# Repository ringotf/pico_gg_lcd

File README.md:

# Pico GG LCD

Work-in-progress update to Trirosmos' original RP2040 Game Gear mod.

More details on the [SMSPower Forum Thread](https://www.smspower.org/forums/20164-OpenSourceGameGearScreenReplacementPicoGGLCD)

## Project Status

Alpha. Main features have been proof-of-concepted, and a working prototype built based on the WL355608 branch (with minimal bodge-fixes). 
The firmware supports both Game Gear and Master System mode, but no adjustable scaling options yet.

> [!NOTE]
> **The PCB design is likely to see major changes.** The current build includes unneccessary placeholder components to be removed, amongst other things. The [WL355608-Dev](tree/WL355608_dev) branch will be updated with Beta changes first.

## "Working" Features

- 640x480 "HD" 3.5inch LCD WL-355608
- HDMI video output with stereo audio using [ikjordan PicoDVI branch](https://github.com/ikjordan/picodvi)
- LED Brightness control with Brightness Wheel
- On-Screen menu. For menu items. And other things.
- GG Mode at 4x horizontal, 3x vertical scaling
- SMS mode at 2x scaling
- [Installation Ribbon](#installation-ribbon)
- 3d printable screen holder

### Demo Video Link (Quiet/NoAudio):

### Another with better audio:

### PCB (Alpha Prototype 4)

## Issues/Upcoming Changes/ToDo

- The LCD connector ribbon is likely to be rotated 180 degrees, will make soldering easier for both LCD and HDMI connectors.
- The op-amps used for audio capture will probably be changed for a dual-op-amp instead of two singles.
- Audio has lots of interference, could be from the LCD mod, could be from the GG.
- The XC6206 3.3v regulator was used to try and eliminate noise from the Pico's onboard regulator interferring with ADC, but might be unneccessary now.
- Remove placeholder components in the audio circuit.
- Corrected LED backlight dimming circuit - currently uses 2 GPIO pins, plus a bodge as shown below.
- The GG Clock pin is no longer needed.
- HDMI Hot-Plug-Detect implemented with the spare Pico GPIO pin.
- Installation Ribbon needs updating to remove the GG Clock pin. 
- Memory. Firmware currently uses 2 framebuffers to help prevent tearing, but with all the other features the Pico is starting to stretch its 264KB RAM... rotating the LCD connector so the LCD is mounted up-right might help allow a single framebuffer and recover some memory for other features.
- The shift registers probably have more performance in them, might be able to work with 2 instead of 3 - might not be worth finding out?

### RP2040 vs RP2350B

Instead of using serial->parallel shift registers to implement the LCD RGB444 input, we could use the extra pins of the Pico2 48-GPIO RP2350B. These are more expensive even after excluding the cost of the 3x 74HC595 shift registers needed for the RP2040, but would simplify the PCB a lot... It was fun to make the project work on an RP2040!

Plus the extra ram of the RP2350 (520KB vs 264KB) will help allow other features to be added to the firmware.

## How It Works

The Game Gear outputs serial RGB444, which is captured using PIO programs and stored in a 16-Bit framebuffer. 
- GG video capture uses 7 GPIO pins: 4 data + 3 control. (*6 without GG Clock now, but anyway)
- PicoDVI output uses 8 GPIO pins.
- LED Backlight brightness control uses 2 GPIO pins.
- LCD requires 3 control signals, Reset, Clock and Data-Enable.

This is 20 pins for capture, HDMI output and LCD control, leaving **10** pins from the 30 GPIO Ultimate Pico.

The LCD expects parallel RGB for 640x480 60Hz. For RGB444 the lcd needs **12** input lines.

To feed the LCD with 12 data inputs, we can use serial-to-parallel shift registers to read data from the Pico serially over a few pins, and send to the LCD over 12 parallel pins.

Although the shift registers have their own timing limits, by using a combination of multiple registers and reusing the same data (scale the image horizontally by clocking the LCD up to 4 times) we can reduce the load on the individual register.

The outputs from the shift registers are interleaved to the LCD to avoid requiring any bit-shifting from the frame buffer.

So the Pico outputs 160 pixels of 12 bit data, with 4 bits per shift register clock to 3 shift registers, and then clocks the LCD 4x for an effective 640 pixels.
Using 5 GPIO pins: 3 MOSI, 1 shift register Latch, 1 shift register clock.

Which leaves a few GPIO pins for audio capture!

### Shift Register Diagram

Hopefully this diagram helps visually explain how the shift registers are wired in:

## Build Pics (Including backlight bodge)

### Assembled PCB Test

### Main Board Installed

### Main Board Testing

### Awaiting Closure

### Completed Build

## Installation Ribbon

There is an FPC Installation Ribbon project for easy soldering to the game gear main board. This is designed for the arms to be folded out to reach the various solder points.

## Schematic

Schematic PDF: [hw/GG_LCD_DIY.pdf](hw/GG_LCD_DIY.pdf)

## Gerbers/Bom

Main PCB Gerbers & Bom: [hw\jlcpcb\production_files](hw\jlcpcb\production_files)

Installation Ribbon Gerbers & Bom: [hw\InstallationRibbon\jlcpcb\production_files](hw\InstallationRibbon\jlcpcb\production_files)

Full details in the above files and KiCad project, but here's some of the highlights:

| Component | Description | Quantity |  Example Link(s) | 
| --- | --- | --- | --- |
| Pico GG LCD PCB | Printed Circuit Board | x1 |  |
| WL-355608 | 640x480 3.5" LCD<br />(Also sold as "RG35XX Replacement Screen") | x1 | https://www.aliexpress.com/item/1005005669918579.html <br /> https://www.aliexpress.com/item/1005007035513918.html |
| 30-GPIO Ultimate Pico | Purple RP2040 | x1 | https://www.aliexpress.com/item/1005005594351599.html <br /> https://www.aliexpress.com/item/1005007057526637.html |
| 54-Pin FPC Connector | LCD Ribbon Connector - Flip/Drawer "Bottom" | x1 | https://www.aliexpress.com/item/1005006818638048.html <br /> https://www.aliexpress.com/item/1005008569249941.html |
| 24-Pin FPC Connector | Data Connector - Flip/Drawer "Bottom" | x1 | https://www.aliexpress.com/item/1005006818638048.html <br /> https://www.aliexpress.com/item/1005008569249941.html |
| XC6206P332MR-G | 3.3v Regulator | x1 | https://www.aliexpress.com/item/33025330295.html |
| TPS61040DBVR | 20v Regulator | x1 | https://www.aliexpress.com/item/1005007852981529.html |
| [74HC595D](docs/sn74hc595.pdf) | Serial->Parallel Shift Registers | x3 | https://www.aliexpress.com/item/1005009410525894.html |
| [74HC165D](docs/sn74hc165.pdf) | Parallel->Serial Shift Register | x1 | https://www.aliexpress.com/item/1005009410525894.html |
| [SN74LVC4245APWR](docs/sn74lvc4245a.pdf) | Level-Shifting Transceiver | x1 | https://www.aliexpress.com/item/1005009206069625.html <br /> https://www.aliexpress.com/item/1005011552818805.html |
| [LMV321IDBVR](docs/lmv321.pdf) | Single Op-Amp | x2 | https://www.aliexpress.com/item/1005006127706764.html |
| HDMI Connector |  | x1 Optional | https://www.aliexpress.com/item/1005001412266648.html |
| DIY HDMI Connector | (See note below) | x2 Optional | https://www.aliexpress.com/item/1005004318851140.html <br /> https://www.aliexpress.com/item/1005006437300837.html |
| 20pin 0.5mm FFC | Flat cable for HDMI connectors<br />(Cheap but unshielded) | x1 Optional | https://www.aliexpress.com/item/1005007561337665.html |

Plus inductor, ferrite bead, diodes, capacitors, resistors, resistor network/arrays.

### DIY HDMI Cable Note

> [!WARNING]
> For DIY HDMI Cable, you need to buy **both Male and Female connector ends from the same listing** to ensure compatability with each other. 

Multiple listings included just as examples. If you mix-and-match across listings you might find the connector boards have different pinouts.

The cable requires a Type-A1 Male connector (the standard type) to connect to the PCB, plus a Female receptacle connector to be mounted inside the case, such as the Standard Type-A (often A4), or Micro-HDMI (often D4), or Mini-HDMI (Often C4) plus a 20cm FFC ribbon to join them together. (15cm is probably ok too)

The Micro-HDMI female connector is ideal for the minimising the size of the hole in the case, but still requires an appropriate Micro-HDMI cable or adapter to connect to a TV.

### DIY HDMI Examples 

### Micro-HDMI Shell Hole

### Micro-HDMI Connector Mounted

### Complete Micro-HDMI Install

### Don't Do This! Careful how the ribbon folds within the case!

# <br/><br/><br/>
### Original project readme for reference. This branch builds upon the fundamentals below:
<br/><br/>
# Pico GG LCD

RP2040-based Game Gear screen replacement kit.
Even a cheapo modern LCD has much, much, much better contrast ratio than the OG screen.

## Building the software

Clone this repository and pull all submodules:
```Bash
git clone https://github.com/Trirosmos/pico_gg_lcd
cd pico_gg_lcd
git submodule update --init --recursive
```

Then, run `sw/build.sh`:

```Bash
cd sw
mkdir build
cd build
cmake ../CMakeLists.txt
make
```

This should generate an uf2 file you can upload to the RP2040;

## Building the hardware

Componentes you'll need and their approximate cost:

- Pico GG LCD PCB ($5)
- [PMOD HDMI adapter board](https://aliexpress.com/w/wholesale-pmod%2525252dhdmi.html?spm=a2g0o.detail.search.0) ($4) 
- [54-pin FPC connector adapter board](https://aliexpress.com/item/32827105259.html) ($2)
- [LQ035NC111 LCD module](https://aliexpress.com/w/wholesale-LQ035NC111.html?spm=a2g0o.home.search.0) ($10)
- [RP2040 board that exposes all 30 GPIOs](https://aliexpress.com/item/1005003796653297.html) ($4)
- BS170 or similar NMOSFET ($0.3)
- ~470uH axial THT inductor ($0.2)
- 2x SOD-123 Schottky diode ($0.4)
- 10k 0805 resistor ($0.05)
- 100k 0805 resistor ($0.05)
- 100nF 0805 resistor ($0.05)
- 100uF 0805 resistor ($0.05)
- 22uF 0805 resistor ($0.05)

Total approximate BOM cost: $26

First assemble passive components and transistor, then the RP2040 board and leave the FPC connector to be connected last.
The final board should look something like this, sans the bodge wire:

## How Game Gear video signals work

The Game Gear ASIC generates digital video signals that the LCD drivers in the LCD ribbon use to drive the actual display segments.

In NTSC mode, i.e, when test pad T10 is connected to +5V, the timings of the signals from the ASIC closely resemble what one would expect from a console like the Master System. All screen replacement kits run the Game Gear in this mode, as far as I'm aware. 

The communication protocol used between the ASIC and the LCD drivers in this mode is [well documented](https://www.retrosix.wiki/va0va1-lcd-interface-game-gear) and essentially boils down to:

- 32 MHz pixel clock (same as the main system clock)
- 4 bit data bus carrying one channel of color data at a time
- VSync signal
- HSync signal

## How the RP2040 captures GG video

One of the PIOs is takes alongside three DMA channels with building a live framebuffer in RAM with the image data the GG is sending out.

Three PIO SMs are used in the following manner:

- SM0 detects when a frame starts and triggers an IRQ.
- SM1 detects the IRQ from SM0 and starts detecting HSync pulses. It triggers an IRQ when it does.
- SM2 detects the IRQ from SM1 and proceeds to capture pixel data and push it out to the RX FIFO.

One of the DMA channels then takes the 12bpp pixel data from the PIO RX FIFO and saves it into RAM.

Finally, one of the CPU cores upscales the image and sends it out to the LCD.

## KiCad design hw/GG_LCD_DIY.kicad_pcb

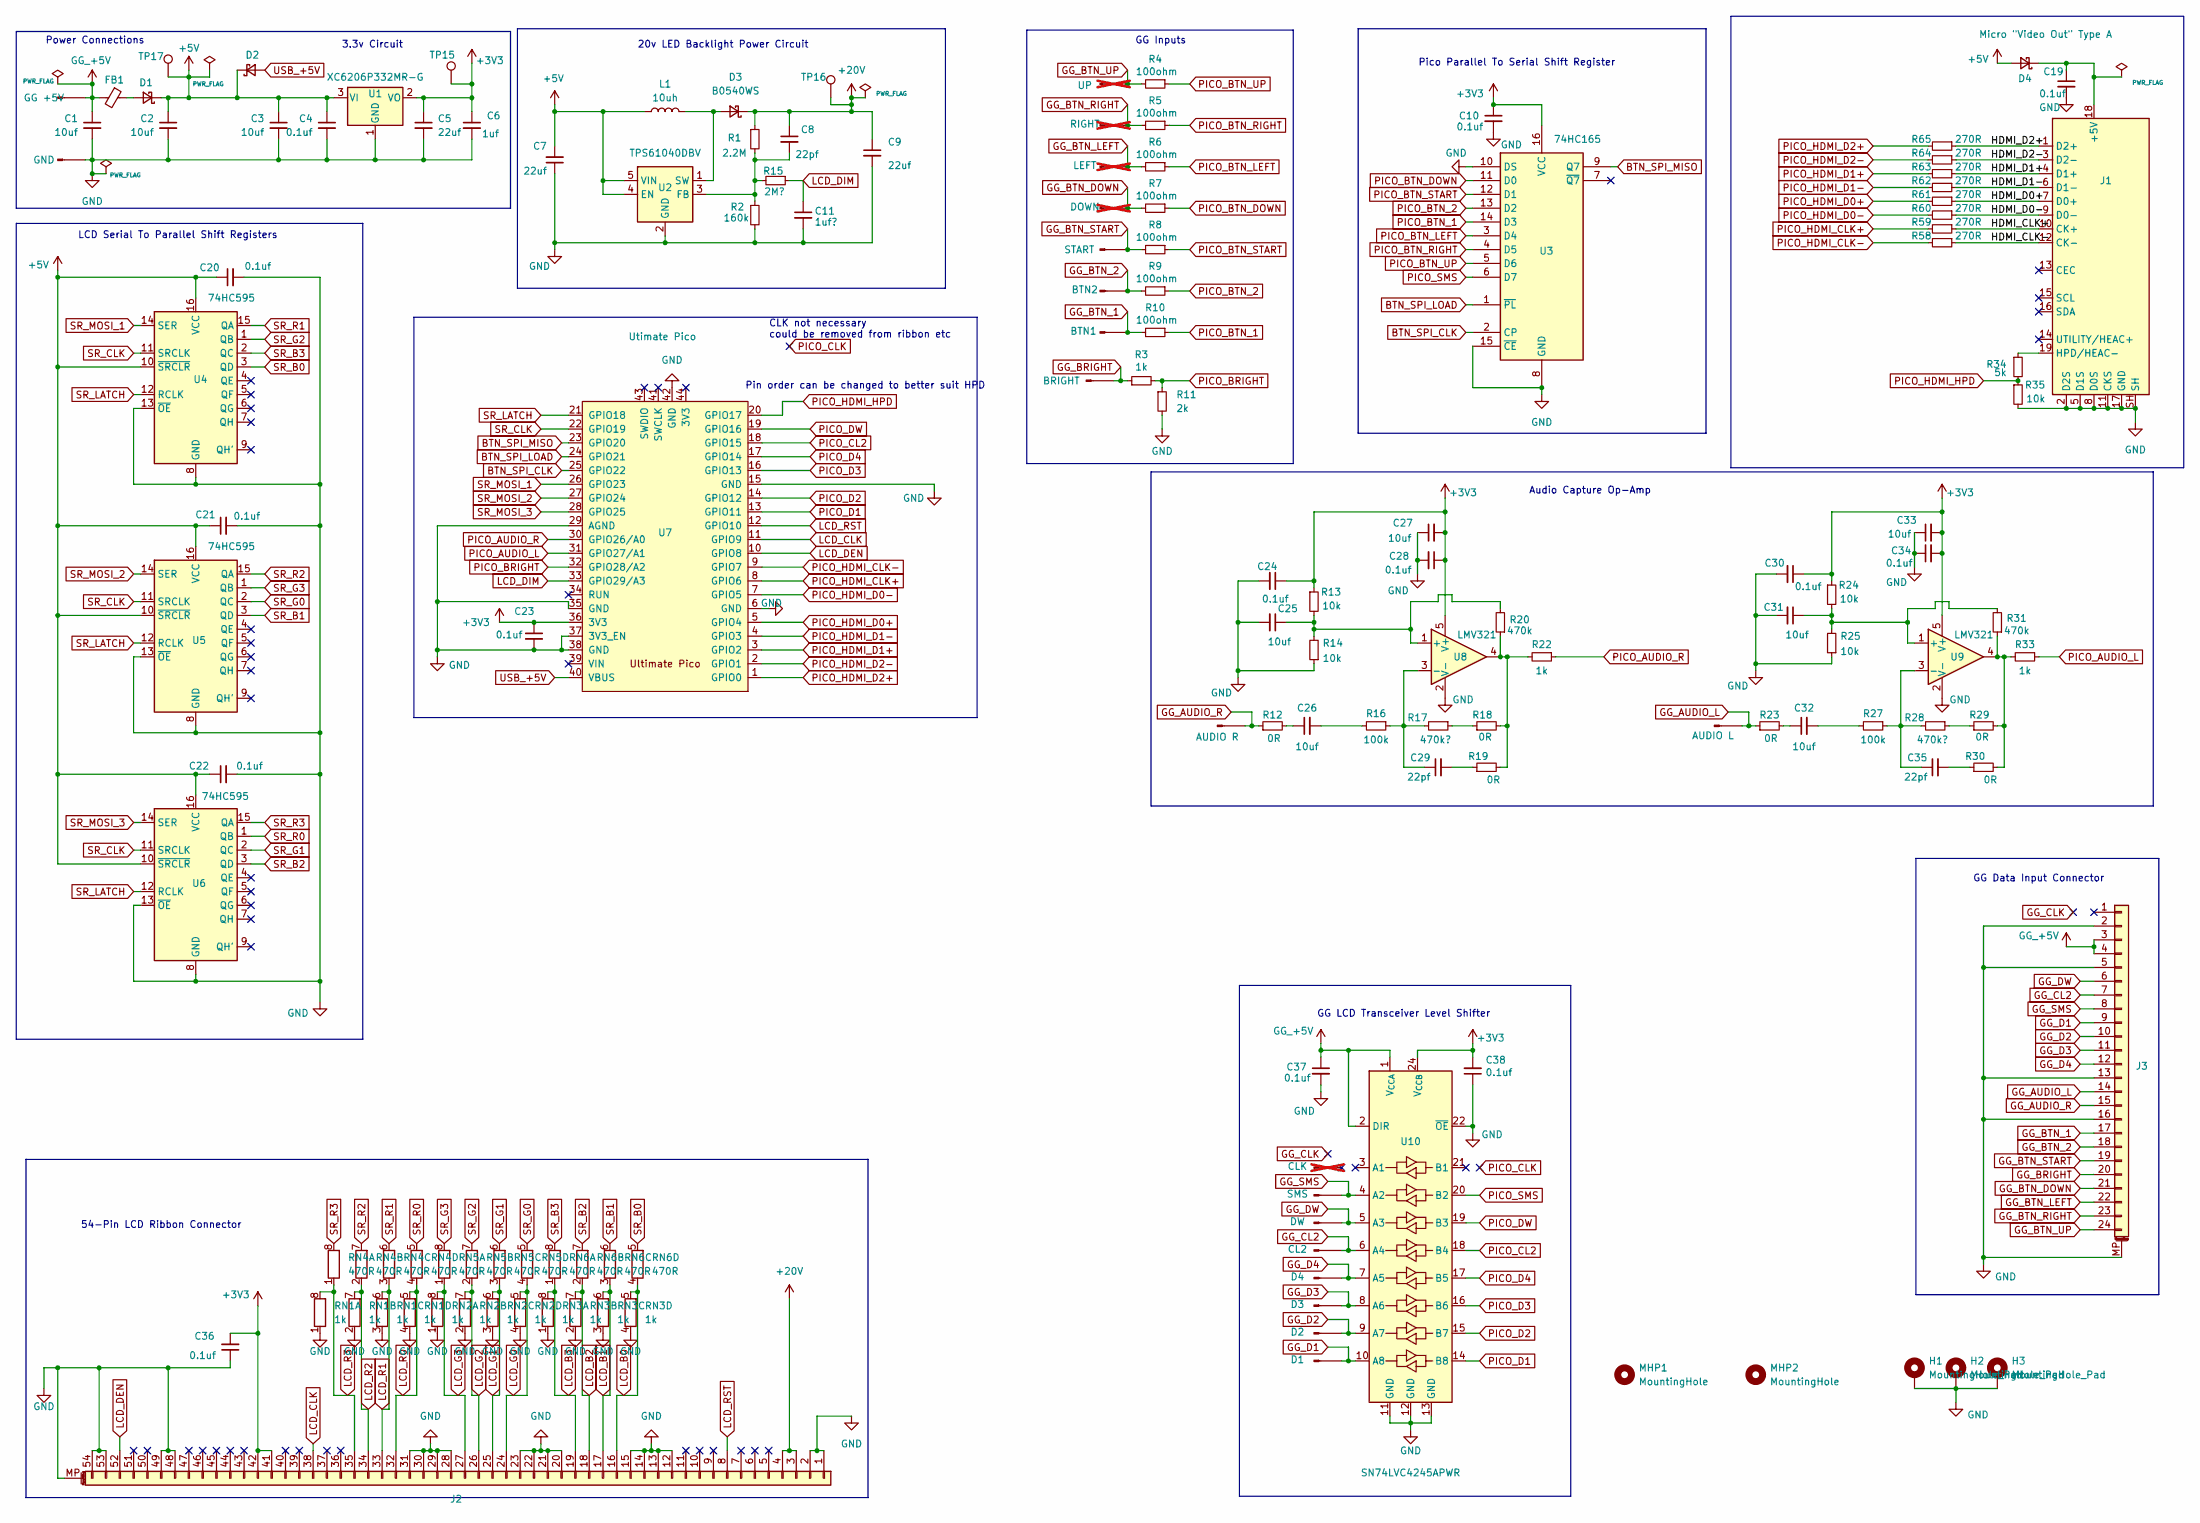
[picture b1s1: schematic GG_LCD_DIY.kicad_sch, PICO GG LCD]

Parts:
C1, C2, C3, C27, C33: 10uf; C_0402_1005Metric_Pad0.74x0.62mm_HandSolder
C4, C10, C19, C20, C21, C22, C23, C28, C34, C36, C37, C38: 0.1uf; C_0402_1005Metric_Pad0.74x0.62mm_HandSolder
C5, C7: 22uf; C_0603_1608Metric_Pad1.08x0.95mm_HandSolder
C6: 1uf; C_0402_1005Metric_Pad0.74x0.62mm_HandSolder
C8: 22pf; C_0402_1005Metric_Pad0.74x0.62mm_HandSolder
C9: 22uf; C_0805_2012Metric_Pad1.18x1.45mm_HandSolder
C11: 1uf?; C_0805_2012Metric_Pad1.18x1.45mm_HandSolder
C24, C30: 0.1uf; C_0805_2012Metric_Pad1.18x1.45mm_HandSolder
C25, C26, C31, C32: 10uf; C_0805_2012Metric_Pad1.18x1.45mm_HandSolder
C29, C35: 22pf; C_0805_2012Metric_Pad1.18x1.45mm_HandSolder
D1, D2, D3, D4: B0540WS; D_SOD-323_HandSoldering
FB1: GZ2012D601TF; L_0805_2012Metric_Pad1.15x1.40mm_HandSolder
H1, H2, H3: MountingHole_Pad; MountingHole_2.2mm_M2_ISO7380_Pad
J1: Micro "Video Out" Type A; HDMI_A_Molex_208658-1001_Horizontal
J2: Conn_01x54; 1x54 FPC Connector 0.5mm HandSolder
J3: 01x24 Conn; Jushuo_AFC07-S24FCA-00_1x24-1MP_P0.50_Horizontal
L1: 10uh; L_0805_2012Metric_Pad1.15x1.40mm_HandSolder
MHP1, MHP2: MountingHole; ToolingHole_1.152mm
R1: 2.2M; R_0603_1608Metric_Pad0.98x0.95mm_HandSolder
R2: 160k; R_0603_1608Metric_Pad0.98x0.95mm_HandSolder
R3: 1k; R_0402_1005Metric_Pad0.72x0.64mm_HandSolder
R4, R5, R6, R7, R8, R9, R10: 100ohm; R_0402_1005Metric_Pad0.72x0.64mm_HandSolder
R11: 2k; R_0402_1005Metric_Pad0.72x0.64mm_HandSolder
R12, R18, R19, R23, R29, R30: 0R; R_0805_2012Metric_Pad1.20x1.40mm_HandSolder
R13, R14, R24, R25: 10k; R_0805_2012Metric_Pad1.20x1.40mm_HandSolder
R15: 2M?; R_0603_1608Metric_Pad0.98x0.95mm_HandSolder
R16, R27: 100k; R_0805_2012Metric_Pad1.20x1.40mm_HandSolder
R17, R28: 470k?; R_0805_2012Metric_Pad1.20x1.40mm_HandSolder
R20, R31: 470k; R_0805_2012Metric_Pad1.20x1.40mm_HandSolder
R22, R33: 1k; R_0805_2012Metric_Pad1.20x1.40mm_HandSolder
R34: 5k; R_0402_1005Metric_Pad0.72x0.64mm_HandSolder
R35: 10k; R_0402_1005Metric_Pad0.72x0.64mm_HandSolder
R58, R59, R60, R61, R62, R63, R64, R65: 270R; R_0402_1005Metric_Pad0.72x0.64mm_HandSolder
RN1, RN2, RN3: 1k; R_Array_Convex_4x0603
RN4, RN5, RN6: 470R; R_Array_Convex_4x0603
T1: GG +5V; TestPoint_Pad_D1.0mm
T2: GND; TestPoint_Pad_D1.0mm
T3: BRIGHT; TestPoint_Pad_D1.0mm
T4: START; TestPoint_Pad_D1.0mm
T5: BTN2; TestPoint_Pad_D1.0mm
T6: BTN1; TestPoint_Pad_D1.0mm
T7: LEFT; TestPoint_Pad_D1.0mm; not fitted
T8: RIGHT; TestPoint_Pad_D1.0mm; not fitted
T9: UP; TestPoint_Pad_D1.0mm; not fitted
T10: DOWN; TestPoint_Pad_D1.0mm; not fitted
T11: AUDIO L; TestPoint_Pad_D1.0mm
T12: AUDIO R; TestPoint_Pad_D1.0mm
T13: CLK; TestPoint_Pad_D1.0mm; not fitted
T14: SMS; TestPoint_Pad_D1.0mm
T15: DW; TestPoint_Pad_D1.0mm
T16: CL2; TestPoint_Pad_D1.0mm
T17: D4; TestPoint_Pad_D1.0mm
T18: D3; TestPoint_Pad_D1.0mm
T19: D2; TestPoint_Pad_D1.0mm
T20: D1; TestPoint_Pad_D1.0mm
TP15: +3V3; TestPoint_Pad_D1.0mm
TP16: +20V; TestPoint_Pad_D1.0mm
TP17: +5V; TestPoint_Pad_D1.0mm
U1: XC6206P332MR-G; SOT-23_Handsoldering
U2: TPS61040DBV; SOT-23-5_HandSoldering
U3: 74HC165; SO-16_3.9x9.9mm_P1.27mm
U4, U5, U6: 74HC595; SO-16_3.9x9.9mm_P1.27mm
U7: Utimate Pico; RPi_Pico_SMD_TH_NoPads
U8, U9: LMV321; SOT-23-5_HandSoldering
U10: SN74LVC4245APWR; TSSOP-24_4.4x7.8mm_P0.65mm

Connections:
+3V3: C5.1, C6.1, C10.1, C23.1, C24.1, C27.2, C28.1, C30.1, C33.2, C34.2, C36.2, C38.2, J2.41, J2.42, R13.1, R24.1, TP15.1, U1.2 (VO), U3.16 (VCC), U7.36 (3V3), U8.5 (V+), U9.5 (V+), U10.24 (V_{CCB})
+5V: C2.1, C3.1, C4.1, C7.2, C20.1, C21.1, C22.1, D1.1 (K), D2.1 (K), D4.2 (A), L1.1, TP17.1, U1.3 (VI), U2.4 (EN), U2.5 (VIN), U4.10 (~SRCLR), U4.16 (VCC), U5.10 (~SRCLR), U5.16 (VCC), U6.10 (~SRCLR), U6.16 (VCC)
+20V: C8.1, C9.1, D3.1 (K), J2.3, J2.4, R1.1, TP16.1
/HDMI_CLK+: J1.10 (CK+), R59.1
/HDMI_CLK-: J1.12 (CK-), R58.1
/HDMI_D0+: J1.7 (D0+), R61.1
/HDMI_D0-: J1.9 (D0-), R60.1
/HDMI_D1+: J1.4 (D1+), R63.1
/HDMI_D1-: J1.6 (D1-), R62.1
/HDMI_D2+: J1.1 (D2+), R65.1
/HDMI_D2-: J1.3 (D2-), R64.1
BTN_SPI_CLK: U3.2 (CP), U7.25 (GPIO22)
BTN_SPI_LOAD: U3.1 (~PL), U7.24 (GPIO21)
BTN_SPI_MISO: U3.9 (Q7), U7.23 (GPIO20)
GG_+5V: C1.1, C37.1, FB1.2, J3.3, J3.4, T1.1, U10.1 (V_{CCA}), U10.2 (DIR)
GG_AUDIO_L: J3.14, R23.1, T11.1
GG_AUDIO_R: J3.15, R12.1, T12.1
GG_BRIGHT: J3.20, R3.1, T3.1
GG_BTN_1: J3.17, R10.2, T6.1
GG_BTN_2: J3.18, R9.2, T5.1
GG_BTN_DOWN: J3.21, R7.2, T10.1
GG_BTN_LEFT: J3.22, R6.2, T7.1
GG_BTN_RIGHT: J3.23, R5.2, T8.1
GG_BTN_START: J3.19, R8.2, T4.1
GG_BTN_UP: J3.24, R4.2, T9.1
GG_CL2: J3.7, T16.1, U10.6 (A4)
GG_D1: J3.9, T20.1, U10.10 (A8)
GG_D2: J3.10, T19.1, U10.9 (A7)
GG_D3: J3.11, T18.1, U10.8 (A6)
GG_D4: J3.12, T17.1, U10.7 (A5)
GG_DW: J3.6, T15.1, U10.5 (A3)
GG_SMS: J3.8, T14.1, U10.4 (A2)
GND: C1.2, C2.2, C3.2, C4.2, C5.2, C6.2, C7.1, C9.2, C10.2, C11.2, C19.2, C20.2, C21.2, C22.2, C23.2, C24.2, C25.2, C27.1, C28.2, C30.2, C31.2, C33.1, C34.1, C36.1, C37.2, C38.1, H1.1, H2.1, H3.1, J1.2 (D2S), J1.5 (D1S), J1.8 (D0S), J1.11 (CKS), J1.17 (GND), J1.SH, J2.1, J2.2, J2.12, J2.13, J2.14, J2.15, J2.20, J2.21, J2.22, J2.23, J2.28, J2.29, J2.30, J2.31, J2.48, J2.49, J2.53, J2.54, J2.MP (MountPin), J3.2, J3.5, J3.13, J3.16, J3.MP (MountPin), R2.2, R11.2, R14.1, R25.1, R35.2, RN1.1 (R1.1), RN1.2 (R2.1), RN1.3 (R3.1), RN1.4 (R4.1), RN2.1 (R1.1), RN2.2 (R2.1), RN2.3 (R3.1), RN2.4 (R4.1), RN3.1 (R1.1), RN3.2 (R2.1), RN3.3 (R3.1), RN3.4 (R4.1), T2.1, U1.1 (GND), U2.2 (GND), U3.8 (GND), U3.10 (DS), U3.15 (~CE), U4.8 (GND), U4.13 (~OE), U5.8 (GND), U5.13 (~OE), U6.8 (GND), U6.13 (~OE), U7.6 (GND), U7.15 (GND), U7.29 (AGND), U7.35 (GND), U7.37 (3V3_EN), U7.38 (GND), U7.42 (GND), U8.2 (V-), U9.2 (V-), U10.11 (GND), U10.12 (GND), U10.13 (GND), U10.22 (~OE)
LCD_B0: J2.16, RN3.5 (R4.2), RN6.4 (R4.1)
LCD_B1: J2.17, RN3.6 (R3.2), RN6.3 (R3.1)
LCD_B2: J2.18, RN3.7 (R2.2), RN6.2 (R2.1)
LCD_B3: J2.19, RN3.8 (R1.2), RN6.1 (R1.1)
LCD_CLK: J2.38, U7.11 (GPIO9)
LCD_DEN: J2.52, U7.10 (GPIO8)
LCD_DIM: C11.1, R15.1, U7.33 (GPIO29/A3)
LCD_G0: J2.24, RN2.5 (R4.2), RN5.4 (R4.1)
LCD_G1: J2.25, RN2.6 (R3.2), RN5.3 (R3.1)
LCD_G2: J2.26, RN2.7 (R2.2), RN5.2 (R2.1)
LCD_G3: J2.27, RN2.8 (R1.2), RN5.1 (R1.1)
LCD_R0: J2.32, RN1.5 (R4.2), RN4.4 (R4.1)
LCD_R1: J2.33, RN1.6 (R3.2), RN4.3 (R3.1)
LCD_R2: J2.34, RN1.7 (R2.2), RN4.2 (R2.1)
LCD_R3: J2.35, RN1.8 (R1.2), RN4.1 (R1.1)
LCD_RST: J2.8, U7.12 (GPIO10)
unnamed: C26.1, R12.2
unnamed: C26.2, R16.2
unnamed: C29.2, R19.1
unnamed: C32.1, R23.2
unnamed: C32.2, R27.2
unnamed: C35.2, R30.1
unnamed: D1.2 (A), FB1.1
unnamed: D3.2 (A), L1.2, U2.1 (SW)
unnamed: C19.1, D4.1 (K), J1.18 (+5V)
unnamed: J1.19 (HPD/HEAC-), R34.1
unnamed: R17.1, R18.1
unnamed: R18.2, R19.2, R20.1, R22.2, U8.4
unnamed: R28.1, R29.1
unnamed: R29.2, R30.2, R31.1, R33.2, U9.4
unnamed: C8.2, R1.2, R2.1, R15.2, U2.3 (FB)
unnamed: C25.1, R13.2, R14.2, R20.2, U8.1 (+)
unnamed: C29.1, R16.1, R17.2, U8.3 (-)
unnamed: C31.1, R24.2, R25.2, R31.2, U9.1 (+)
unnamed: C35.1, R27.1, R28.2, U9.3 (-)
PICO_AUDIO_L: R33.1, U7.31 (GPIO27/A1)
PICO_AUDIO_R: R22.1, U7.30 (GPIO26/A0)
PICO_BRIGHT: R3.2, R11.1, U7.32 (GPIO28/A2)
PICO_BTN_1: R10.1, U3.14 (D3)
PICO_BTN_2: R9.1, U3.13 (D2)
PICO_BTN_DOWN: R7.1, U3.11 (D0)
PICO_BTN_LEFT: R6.1, U3.3 (D4)
PICO_BTN_RIGHT: R5.1, U3.4 (D5)
PICO_BTN_START: R8.1, U3.12 (D1)
PICO_BTN_UP: R4.1, U3.5 (D6)
PICO_CL2: U7.18 (GPIO15), U10.18 (B4)
PICO_D1: U7.13 (GPIO11), U10.14 (B8)
PICO_D2: U7.14 (GPIO12), U10.15 (B7)
PICO_D3: U7.16 (GPIO13), U10.16 (B6)
PICO_D4: U7.17 (GPIO14), U10.17 (B5)
PICO_DW: U7.19 (GPIO16), U10.19 (B3)
PICO_HDMI_CLK+: R59.2, U7.8 (GPIO6)
PICO_HDMI_CLK-: R58.2, U7.9 (GPIO7)
PICO_HDMI_D0+: R61.2, U7.5 (GPIO4)
PICO_HDMI_D0-: R60.2, U7.7 (GPIO5)
PICO_HDMI_D1+: R63.2, U7.3 (GPIO2)
PICO_HDMI_D1-: R62.2, U7.4 (GPIO3)
PICO_HDMI_D2+: R65.2, U7.1 (GPIO0)
PICO_HDMI_D2-: R64.2, U7.2 (GPIO1)
PICO_HDMI_HPD: R34.2, R35.1, U7.20 (GPIO17)
PICO_SMS: U3.6 (D7), U10.20 (B2)
SR_B0: RN6.5 (R4.2), U4.3 (QD)
SR_B1: RN6.6 (R3.2), U5.3 (QD)
SR_B2: RN6.7 (R2.2), U6.3 (QD)
SR_B3: RN6.8 (R1.2), U4.2 (QC)
SR_CLK: U4.11 (SRCLK), U5.11 (SRCLK), U6.11 (SRCLK), U7.22 (GPIO19)
SR_G0: RN5.5 (R4.2), U5.2 (QC)
SR_G1: RN5.6 (R3.2), U6.2 (QC)
SR_G2: RN5.7 (R2.2), U4.1 (QB)
SR_G3: RN5.8 (R1.2), U5.1 (QB)
SR_LATCH: U4.12 (RCLK), U5.12 (RCLK), U6.12 (RCLK), U7.21 (GPIO18)
SR_MOSI_1: U4.14 (SER), U7.26 (GPIO23)
SR_MOSI_2: U5.14 (SER), U7.27 (GPIO24)
SR_MOSI_3: U6.14 (SER), U7.28 (GPIO25)
SR_R0: RN4.5 (R4.2), U6.1 (QB)
SR_R1: RN4.6 (R3.2), U4.15 (QA)
SR_R2: RN4.7 (R2.2), U5.15 (QA)
SR_R3: RN4.8 (R1.2), U6.15 (QA)
USB_+5V: D2.2 (A), U7.40 (VBUS)

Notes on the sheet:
Audio Capture Op-Amp
20v LED Backlight Power Circuit
Pico Parallel To Serial Shift Register
Power Connections
CLK not necessary could be removed from ribbon etc
3.3v Circuit
GG Inputs
GG LCD Transceiver Level Shifter
Pin order can be changed to better suit HPD
54-Pin LCD Ribbon Connector
GG Data Input Connector
LCD Serial To Parallel Shift Registers

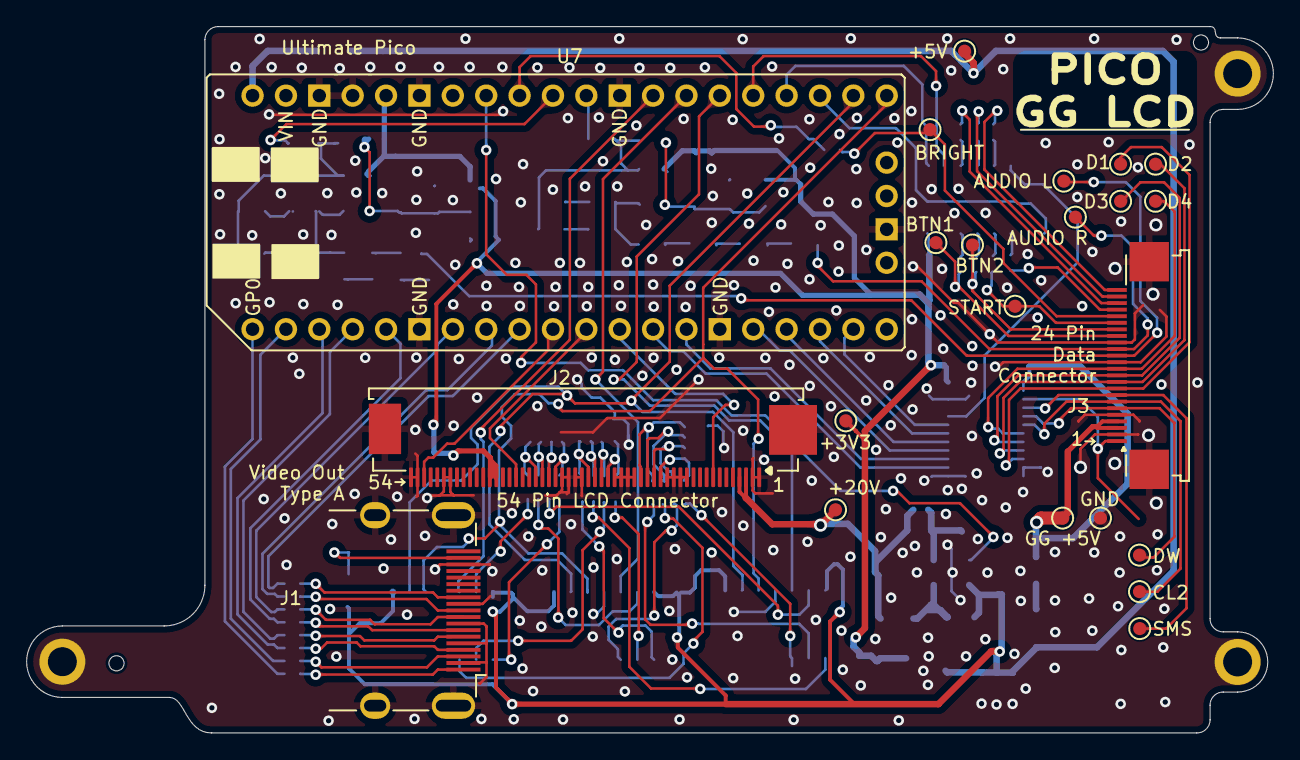
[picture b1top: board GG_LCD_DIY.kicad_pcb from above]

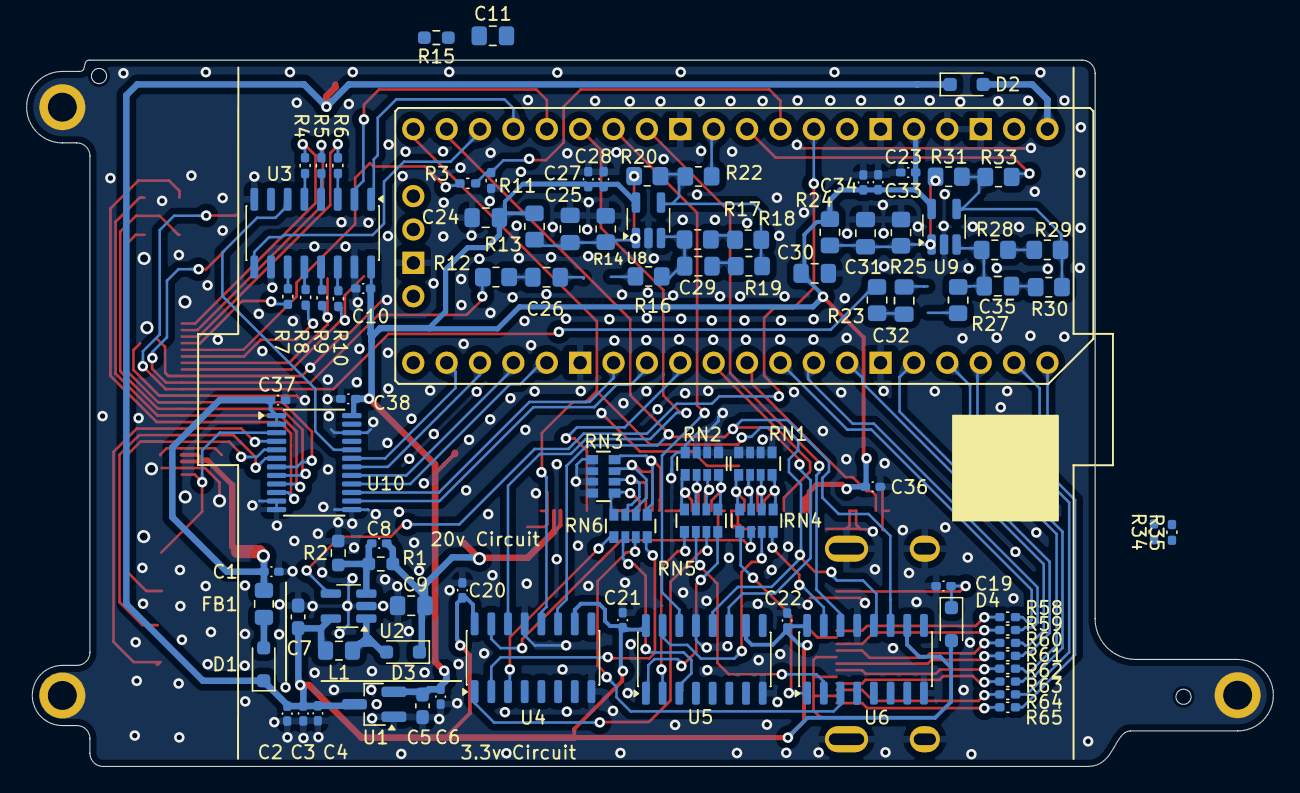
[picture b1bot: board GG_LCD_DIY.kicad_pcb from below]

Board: 2 copper layers, 94.9 x 53.8 mm, 120 parts (92 on the bottom side), 112 nets.

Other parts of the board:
LCD1: lcd_template_with_ribbon

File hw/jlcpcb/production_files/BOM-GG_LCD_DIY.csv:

Comment,Designator,Footprint,LCSC,Quantity
0.1uf,"C10,C19,C20,C21,C22,C23,C28,C34,C36,C37,C38,C4",C_0402_1005Metric_Pad0.74x0.62mm_HandSolder,C1525,12
0.1uf,"C24,C30",C_0805_2012Metric_Pad1.18x1.45mm_HandSolder,C28233,2
0R,"R12,R15,R18,R19,R21,R23,R26,R29,R30,R32",R_0805_2012Metric_Pad1.20x1.40mm_HandSolder,C17477,10
100k,"R16,R27",R_0805_2012Metric_Pad1.20x1.40mm_HandSolder,C149504,2
100ohm,"R10,R4,R5,R6,R7,R8,R9",R_0402_1005Metric_Pad0.72x0.64mm_HandSolder,C25076,7
10k,"R13,R14,R24,R25",R_0805_2012Metric_Pad1.20x1.40mm_HandSolder,C17414,4
10uf,"C1,C2,C27,C3,C33",C_0402_1005Metric_Pad0.74x0.62mm_HandSolder,C15525,5
10uf,"C25,C26,C31,C32",C_0805_2012Metric_Pad1.18x1.45mm_HandSolder,C15850,4
10uh,L1,L_0805_2012Metric_Pad1.15x1.40mm_HandSolder,C1046,1
160k,R2,R_0603_1608Metric_Pad0.98x0.95mm_HandSolder,C22807,1
1k,R3,R_0402_1005Metric_Pad0.72x0.64mm_HandSolder,C11702,1
1k,"R22,R33",R_0805_2012Metric_Pad1.20x1.40mm_HandSolder,C17513,2
1k,"RN1,RN2,RN3",R_Array_Convex_4x0603,C20197,3
1uf,C6,C_0402_1005Metric_Pad0.74x0.62mm_HandSolder,C52923,1
2.2M,R1,R_0603_1608Metric_Pad0.98x0.95mm_HandSolder,C22976,1
22pf,C8,C_0402_1005Metric_Pad0.74x0.62mm_HandSolder,C1555,1
22pf,"C29,C35",C_0805_2012Metric_Pad1.18x1.45mm_HandSolder,C1804,2
22uf,C9,C_0805_2012Metric_Pad1.18x1.45mm_HandSolder,C45783,1
22uf,"C5,C7",C_0603_1608Metric_Pad1.08x0.95mm_HandSolder,C59461,2
270R,"R58,R59,R60,R61,R62,R63,R64,R65",R_0402_1005Metric_Pad0.72x0.64mm_HandSolder,C25091,8
2k,R11,R_0402_1005Metric_Pad0.72x0.64mm_HandSolder,C4109,1
470R,"RN4,RN5,RN6",R_Array_Convex_4x0603,C25510,3
500k,"R17,R28",R_0805_2012Metric_Pad1.20x1.40mm_HandSolder,C17709,2
74HC165,U3,SO-16_3.9x9.9mm_P1.27mm,C5613,1
74HC595,"U4,U5,U6",SO-16_3.9x9.9mm_P1.27mm,C5947,3
B0540WS,"D1,D2,D3,D4",D_SOD-323_HandSoldering,C7420326,4
GZ2012D601TF,FB1,L_0805_2012Metric_Pad1.15x1.40mm_HandSolder,C1017,1
LMV321,"U8,U9",SOT-23-5_HandSoldering,C7972,2
SN74LVC4245APWR,U10,TSSOP-24_4.4x7.8mm_P0.65mm,C7859,1
TPS61040DBV,U2,SOT-23-5_HandSoldering,C7722,1
XC6206P332MR-G,U1,SOT-23_Handsoldering,C5446,1

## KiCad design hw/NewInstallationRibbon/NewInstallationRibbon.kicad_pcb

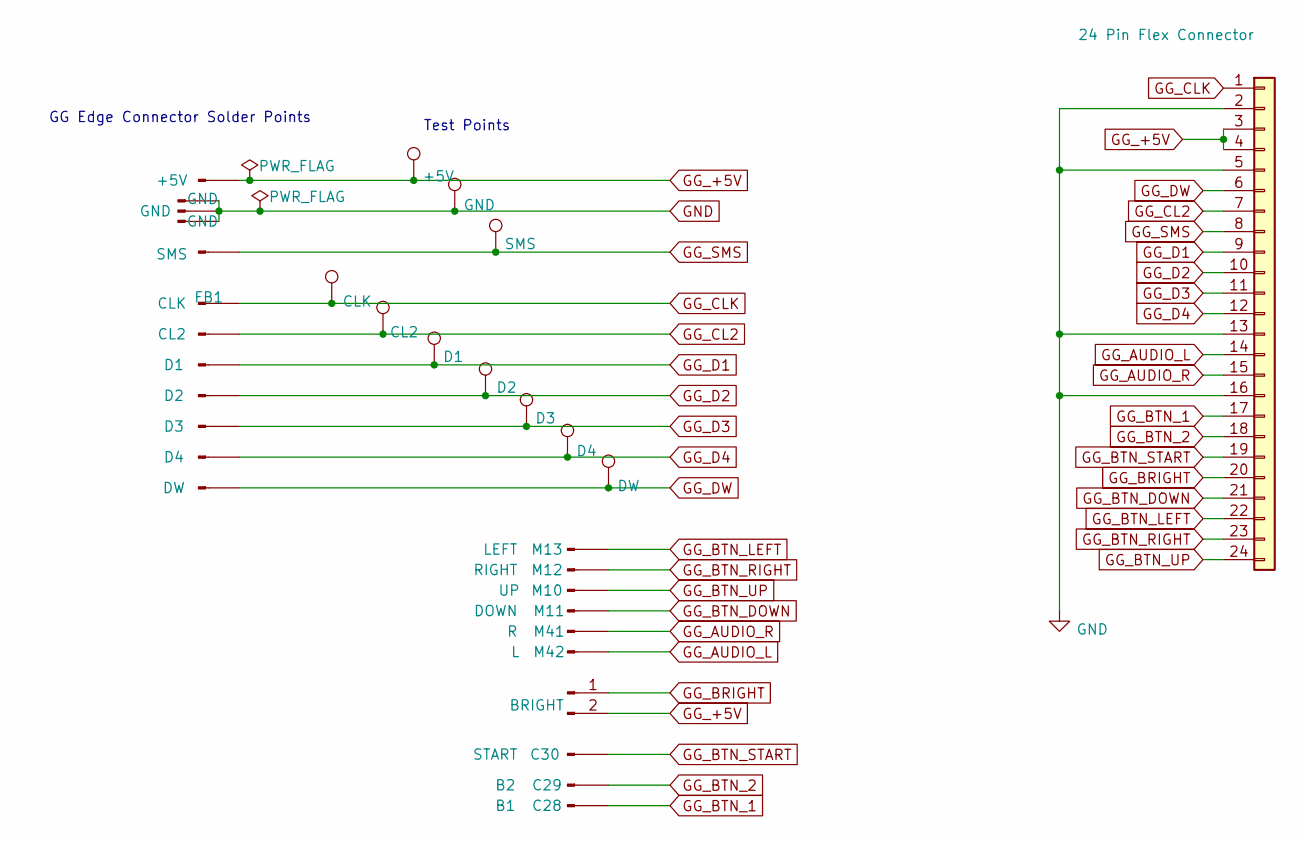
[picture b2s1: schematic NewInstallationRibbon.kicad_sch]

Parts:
J1: +5V; TestPoint_THTPad_D2.5mm_Drill1.2mm
J2, J15, J16: GND; TestPoint_THTPad_D2.5mm_Drill1.2mm
J3: CLK; TestPoint_THTPad_D2.5x2.5mm_Drill1.2mm
J4: SMS; TestPoint_THTPad_D2.5mm_Drill1.2mm
J5: DW; SolderWirePad_1x01_EdgeWithHole_1x2mm
J6: CL2; SolderWirePad_1x01_EdgeWithHole_1x2mm
J7: D1; SolderWirePad_1x01_EdgeWithHole_1x2mm
J8: D2; SolderWirePad_1x01_EdgeWithHole_1x2mm
J9: D3; SolderWirePad_1x01_EdgeWithHole_1x2mm
J10: D4; SolderWirePad_1x01_EdgeWithHole_1x2mm
J12: LEFT; TestPoint_THTPad_D2.5mm_Drill1.2mm
J13: RIGHT; TestPoint_THTPad_D2.5mm_Drill1.2mm
J14: UP; TestPoint_THTPad_D2.5mm_Drill1.2mm
J17: 24 Pin Flex Connector; Flex Connector 0.5mm 01x24Pin
J18: DOWN; TestPoint_THTPad_D2.5mm_Drill1.2mm
J19: R; TestPoint_THTPad_D2.5mm_Drill1.2mm
J20: L; TestPoint_THTPad_D2.5mm_Drill1.2mm
J21: START; TestPoint_THTPad_D2.5x2.5mm_Drill1.2mm
J22: B2; TestPoint_THTPad_D2.5x2.5mm_Drill1.2mm
J23: B1; TestPoint_THTPad_D2.5x2.5mm_Drill1.2mm
J25: BRIGHT; TestPoint_2Pads_Pitch2.00mm_Drill1.0mm_OneSide
TP1: +5V; TestPoint_Pad_2.0x2.0mm
TP2: GND; TestPoint_Pad_2.0x2.0mm
TP3: CLK; TestPoint_Pad_2.0x2.0mm
TP4: SMS; TestPoint_Pad_2.0x2.0mm
TP5: DW; TestPoint_Pad_2.0x2.0mm
TP6: CL2; TestPoint_Pad_2.0x2.0mm
TP7: D4; TestPoint_Pad_2.0x2.0mm
TP8: D3; TestPoint_Pad_2.0x2.0mm
TP9: D2; TestPoint_Pad_2.0x2.0mm
TP10: D1; TestPoint_Pad_2.0x2.0mm

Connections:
GG_+5V: J1.1, J17.3, J17.4, J25.2, TP1.1
GG_AUDIO_L: J17.14, J20.1
GG_AUDIO_R: J17.15, J19.1
GG_BRIGHT: J17.20, J25.1
GG_BTN_1: J17.17, J23.1
GG_BTN_2: J17.18, J22.1
GG_BTN_DOWN: J17.21, J18.1
GG_BTN_LEFT: J12.1, J17.22
GG_BTN_RIGHT: J13.1, J17.23
GG_BTN_START: J17.19, J21.1
GG_BTN_UP: J14.1, J17.24
GG_CL2: J6.1, J17.7, TP6.1
GG_CLK: J3.1, J17.1, TP3.1
GG_D1: J7.1, J17.9, TP10.1
GG_D2: J8.1, J17.10, TP9.1
GG_D3: J9.1, J17.11, TP8.1
GG_D4: J10.1, J17.12, TP7.1
GG_DW: J5.1, J17.6, TP5.1
GG_SMS: J4.1, J17.8, TP4.1
GND: J2.1, J15.1, J16.1, J17.2, J17.5, J17.13, J17.16, TP2.1

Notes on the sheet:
Test Points
GG Edge Connector Solder Points

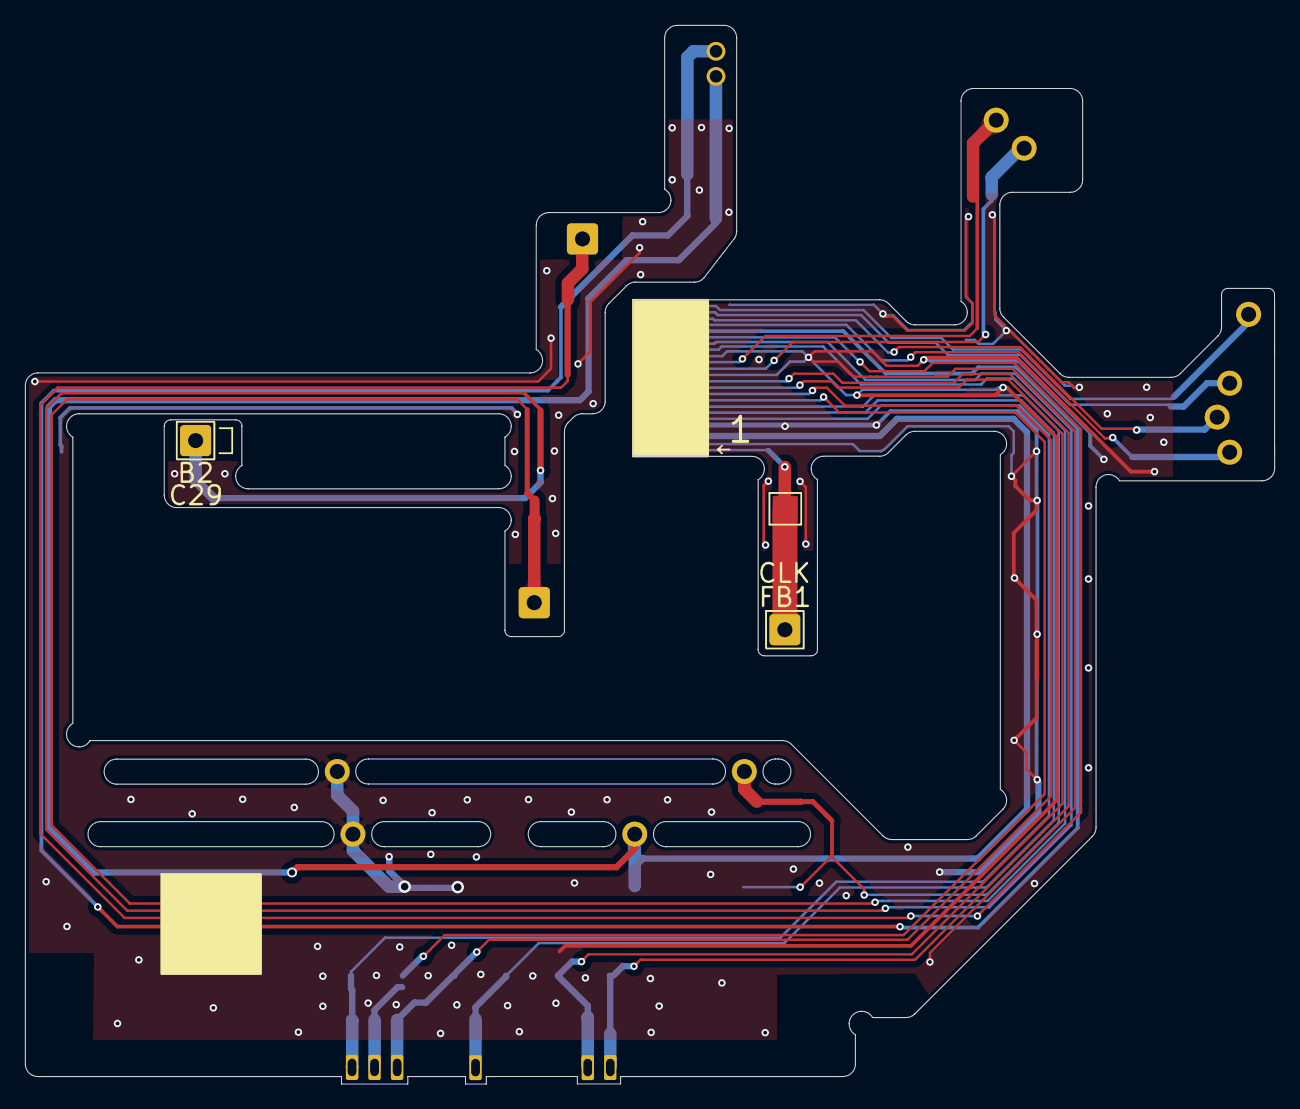
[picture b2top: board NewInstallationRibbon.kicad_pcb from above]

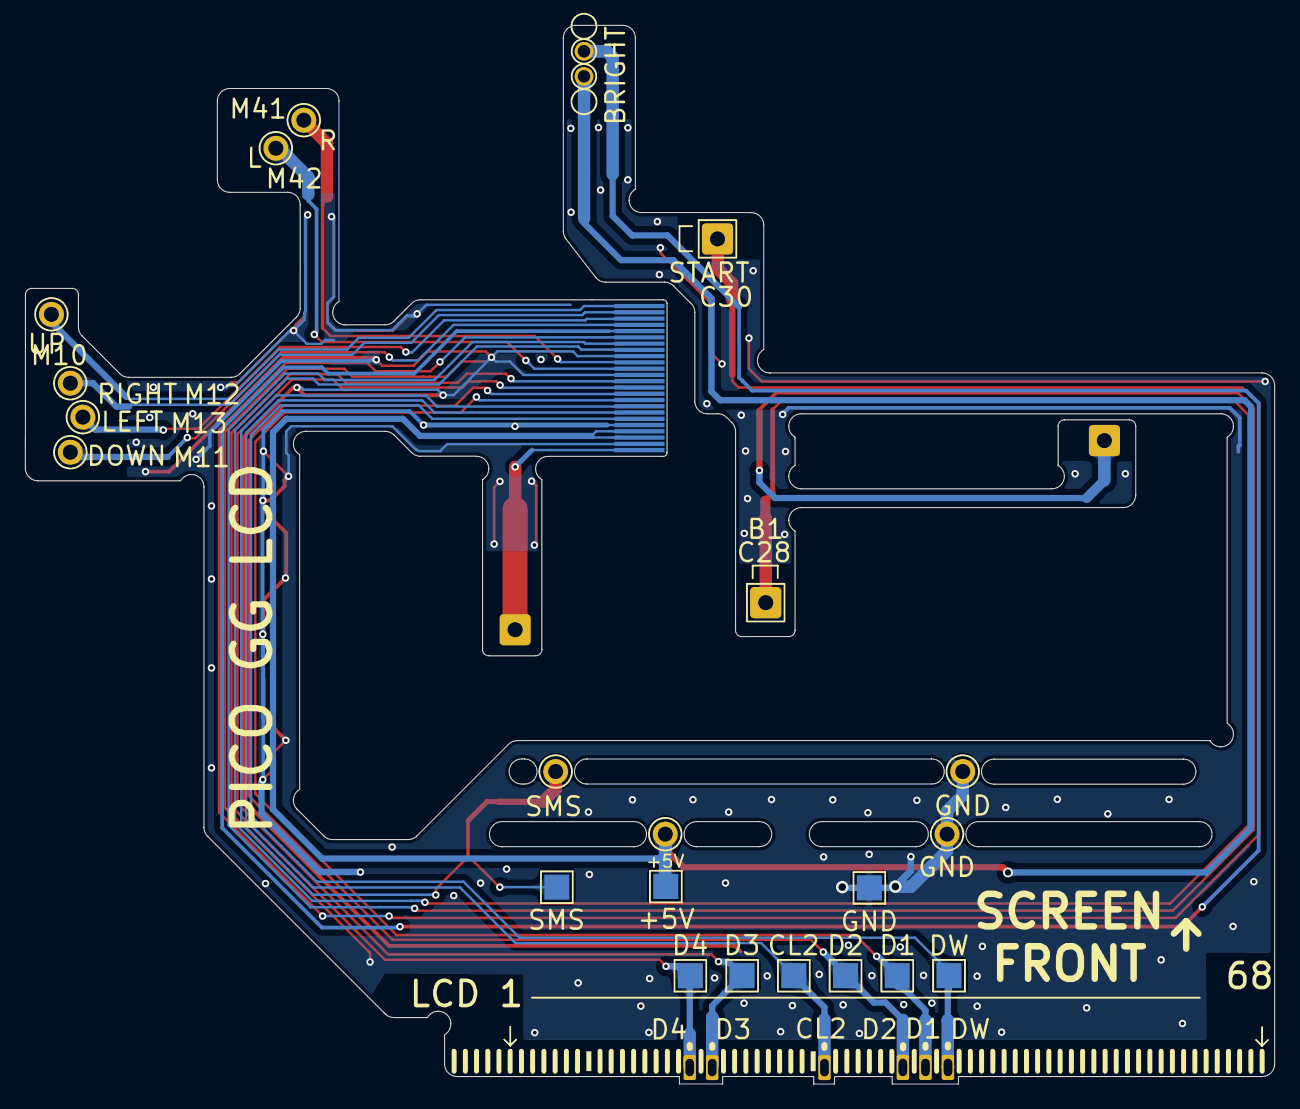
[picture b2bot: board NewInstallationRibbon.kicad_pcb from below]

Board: 2 copper layers, 99.7 x 84.5 mm, 32 parts (29 on the bottom side), 20 nets.
